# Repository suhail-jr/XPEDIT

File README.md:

# XPEDIT
When you are planning to do an adventure journey or trekking to the wild, it is essential to have a device in your backpack that helps you to understand the environment. For my upcoming adventure journey, i planned to build a device that helps me to monitors temperature, humidity, air pressure, and altitude.

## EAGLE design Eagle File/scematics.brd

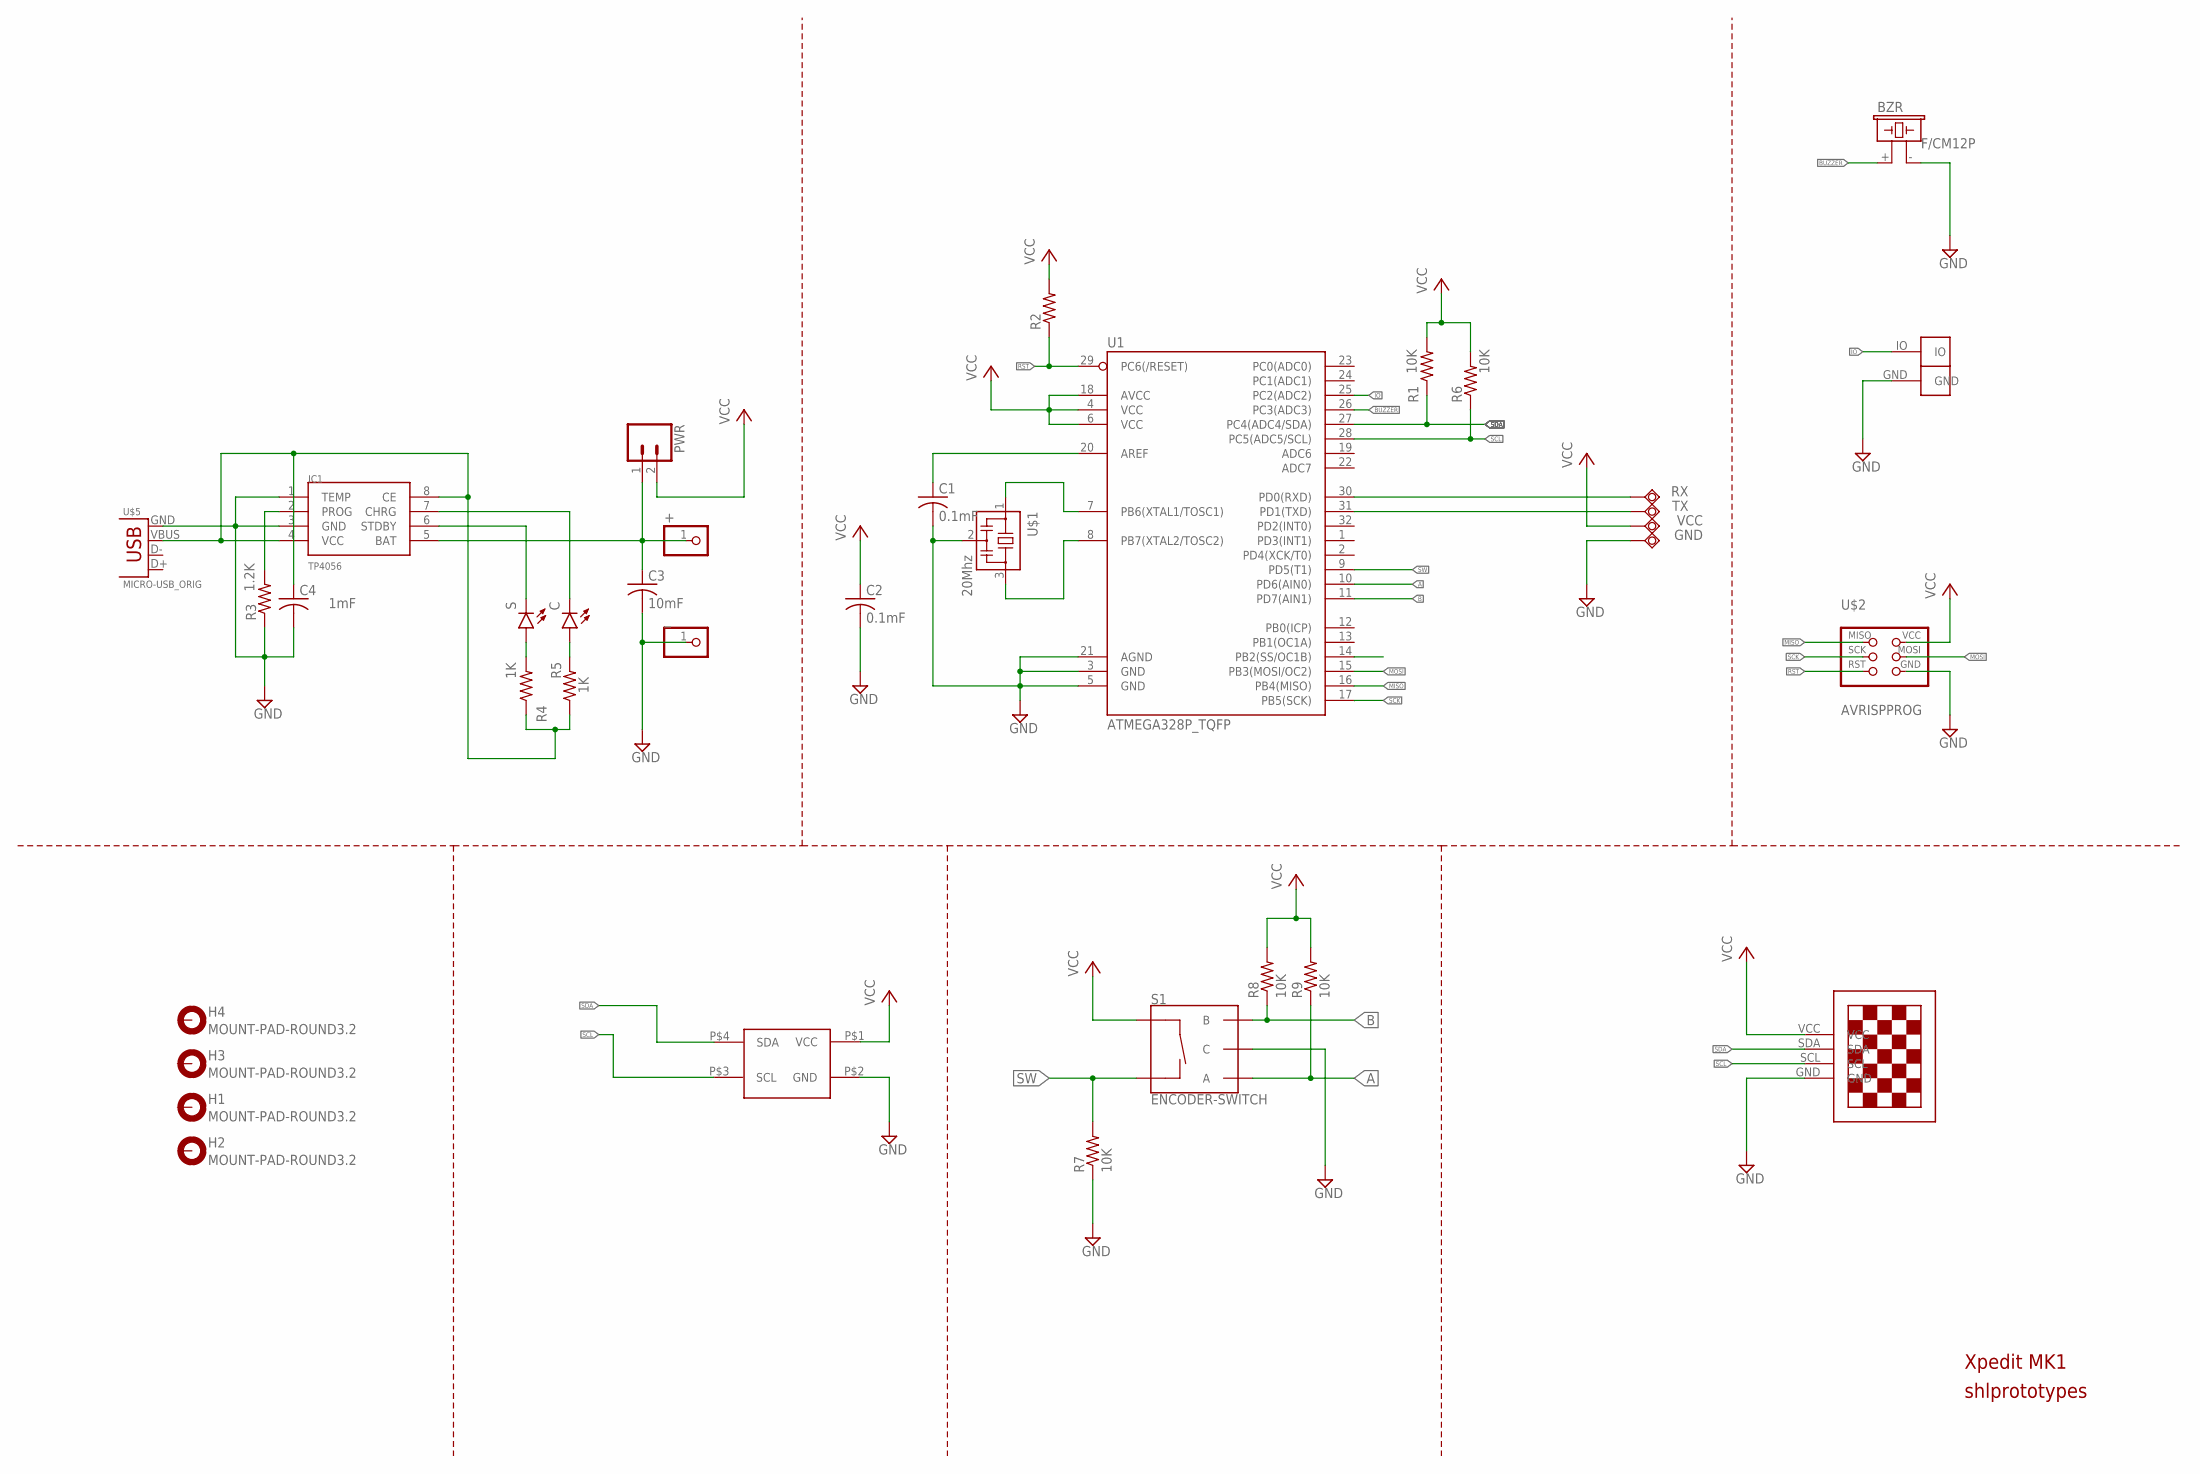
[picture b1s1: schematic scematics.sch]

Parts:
+: PINHD-1X1; 1X01
BZR: F/CM12P
C: LEDSML0805; SML0805
C1, C2: 0.1mF; C0805
C3: 10mF; C0805
C4: 1mF; C0805
GND: TPSQTP16R; TP16R
H1, H2, H3, H4: MOUNT-PAD-ROUND3.2; 3,2-PAD
IC1: TP4056; SOP-8
PWR: CONN_02; 1X02
R1, R6, R7, R8, R9: 10K; R0805
R2: R-US_R0805; R0805
R3: 1.2K; R0805
R4, R5: 1K; R0805
RX: TPSQTP16R; TP16R
S: LEDSML0805; SML0805
S1: ENCODER-SWITCH; ROTARY_ENC_PLAIN
TAPTIC: VIBRARTOR; VIBRATOR
TX: TPSQTP16R; TP16R
U1: ATMEGA328P_TQFP; TQFP32-08
U$1: 20Mhz; EFOBM
U$2: AVRISPPROG; SMD
U$3: BME280
U$4: 13"OLED13"OLED; 1.3"OLED
U$5: MICRO-USB_ORIG; DX4R005HJ5
VCC: TPSQTP16R; TP16R
_: PINHD-1X1; 1X01

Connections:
A: R9.1, S1.A, U1.10 (PD6(AIN0))
B: R8.1, S1.B, U1.11 (PD7(AIN1))
BUZZER: BZR.+ (1), U1.26 (PC3(ADC3))
CS: U1.14 (PB2(SS/OC1B))
GND: BZR.- (2), C1.2, C2.2, C3.2, C4.2, GND.TP, IC1.1 (TEMP), IC1.3 (GND), R3.1, R7.1, S1.C, TAPTIC.GND, U1.3 (GND), U1.5 (GND), U1.21 (AGND), U$1.2, U$2.6 (GND), U$3.P$2 (GND), U$4.GND, U$5.GND, _.1
IO: TAPTIC.IO, U1.25 (PC2(ADC2))
MISO: U1.16 (PB4(MISO)), U$2.1 (MISO)
MOSI: U1.15 (PB3(MOSI/OC2)), U$2.5 (MOSI)
unnamed: U1.7 (PB6(XTAL1/TOSC1)), U$1.1
unnamed: U1.8 (PB7(XTAL2/TOSC2)), U$1.3
unnamed: RX.TP, U1.30 (PD0(RXD))
unnamed: TX.TP, U1.31 (PD1(TXD))
unnamed: +.1, C3.1, IC1.5 (BAT), PWR.1
unnamed: C1.1, U1.20 (AREF)
unnamed: IC1.2 (PROG), R3.2
unnamed: C4.1, IC1.4 (VCC), IC1.8 (CE), R4.1, R5.1, U$5.VBUS
unnamed: IC1.6 (STDBY), S.C
unnamed: C.C, IC1.7 (CHRG)
unnamed: C.A, R5.2
unnamed: R4.2, S.A
RST: R2.1, U1.29 (PC6(/RESET)), U$2.3 (RST)
SCK: U1.17 (PB5(SCK)), U$2.2 (SCK)
SCL: R6.1, U1.28 (PC5(ADC5/SCL)), U$3.P$3 (SCL), U$4.SCL
SDA: R1.1, U1.27 (PC4(ADC4/SDA)), U$3.P$4 (SDA), U$4.SDA
SW: R7.2, S1.SW-, U1.9 (PD5(T1))
VCC: C2.1, PWR.2, R1.2, R2.2, R6.2, R8.2, R9.2, S1.SW+, U1.4 (VCC), U1.6 (VCC), U1.18 (AVCC), U$2.4 (VCC), U$3.P$1 (VCC), U$4.VCC, VCC.TP

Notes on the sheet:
Xpedit MK1
shlprototypes

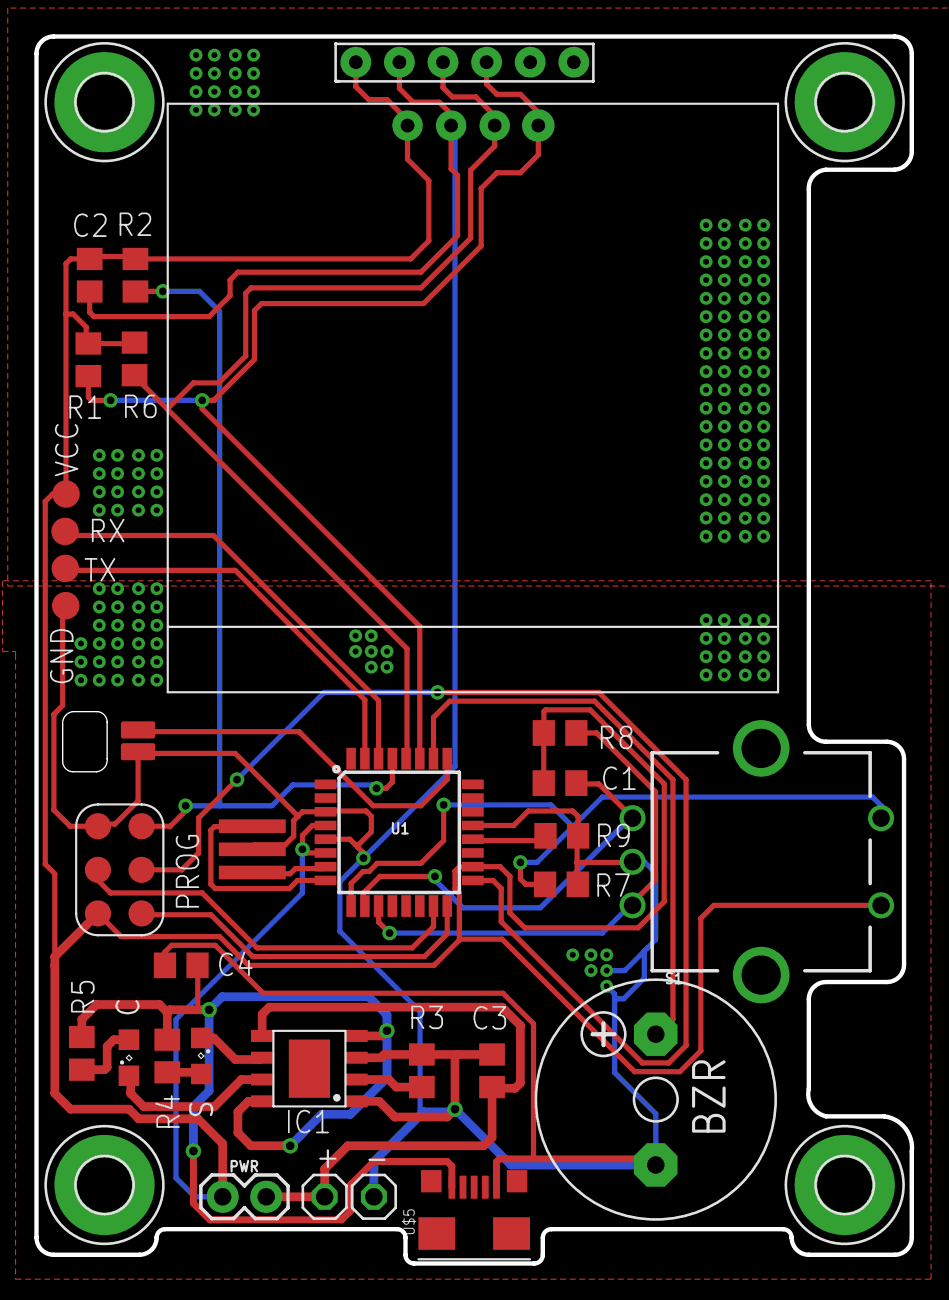
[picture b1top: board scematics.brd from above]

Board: 2 copper layers, 51.0 x 71.5 mm, 36 parts (0 on the bottom side), 25 nets.

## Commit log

2019-07-29 Create Firmware

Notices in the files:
parts and their libraries:
SparkFun-Switches: Licensing: Creative Commons ShareAlike 4.0 International - https://creativecommons.org/licenses/by-sa/4.0
